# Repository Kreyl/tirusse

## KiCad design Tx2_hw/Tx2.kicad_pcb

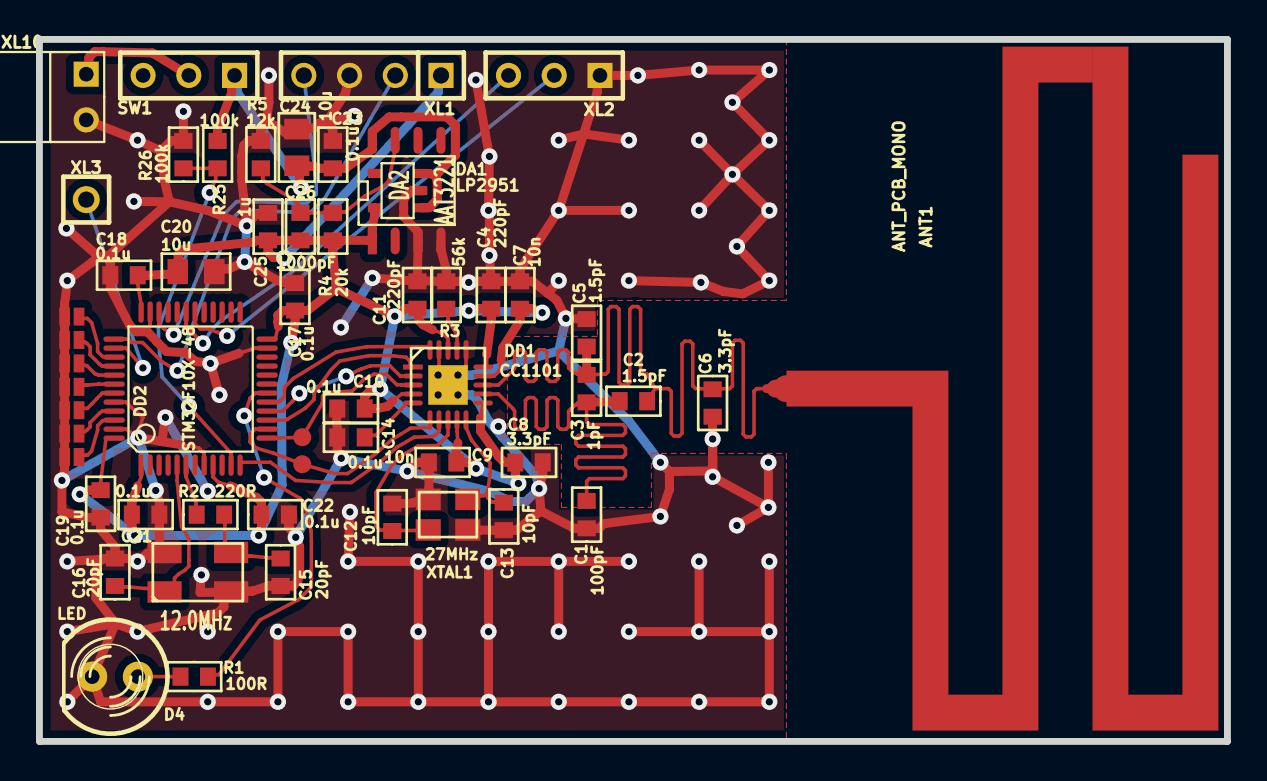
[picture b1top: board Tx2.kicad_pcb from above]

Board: 2 copper layers, 66.0 x 39.0 mm, 55 parts (0 on the bottom side), 35 nets.

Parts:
ANT1: ANT_PCB_MONO; ANT_868_MEANDER
C1: 100pF; CAP_0603
C2, C5: 1.5pF; CAP_0603
C3: 1pF; CAP_0603
C4, C11: 220pF; CAP_0603
C6, C8: 3.3pF; CAP_0603
C7, C9: 10n; CAP_0603
C10, C14, C17, C18, C19, C21, C22, C23: 0.1u; CAP_0603
C12, C13: 10pF; CAP_0603
C15, C16: 20pF; CAP_0603
C20, C24: 10u; CAP_0805
C25: 1u; CAP_0603
C26: 1000pF; CAP_0603
D4: LED; LED-5MM
DA1: LP2951; SO8E
DA2: AAT3221; SOT23-5
DD1: CC1101; QFN20
DD2: STM32F10X-48; LQFP48
F1, F2, F3, F4, F5, F6, F7: FUSE0R; SOLDERFUSE
R1: 100R; RES_0603
R2: 220R; RES_0603
R3: 56k; RES_0603
R4: 20k; RES_0603
R5: 12k; RES_0603
R25, R26: 100k; RES_0603
SW1: SWITCH; SIL-3
TP1, TP2: TESTPOINT; TESTPOINT_1MM
XL1: ST_SWD; SIL-4
XL2: CONN_3; SIL-3
XL3: CONN_1; SIL-1
XL10: PWRCONN; PWRCON2PIN
XTAL1: 27MHz; CRYSTAL_03225C4
XTAL2: 12.0MHz; CRYSTAL_0503x4-4

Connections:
+3.3V: C4.1, C7.1, C8.1, C9.1, C10.1, C11.1, C17.1, C18.1, C19.1, C20.1, C21.1, C22.1, C25.1, C26.1, DA1.1, DA2.5, DD1.4, DD1.9, DD1.11, DD1.14, DD1.15, DD1.18, DD2.1, DD2.9, DD2.24, DD2.36, DD2.48, R4.1, XL1.1
+BATT: C23.1, C24.1, DA1.8, DA2.1, DA2.3, R25.1, SW1.1
/BAT: SW1.2, XL10.1
/CC_CS: DD1.7, DD2.12
/CC_GDO0: DD1.6, DD2.14, TP1.1
/CC_GDO2: DD1.3, DD2.13, TP2.1
/CC_MISO: DD1.2, DD2.16
/CC_MOSI: DD1.20, DD2.17
/CC_SCK: DD1.1, DD2.15
/Debug: DD2.38, XL3.1
/RF1: C1.2, C2.2, C3.1, DD1.12
/RF2: ANT1.1, C2.1, C3.2, C5.1, C6.1, DD1.13
/RX1: DD2.31, XL2.3
/SWCLK: DD2.37, XL1.2
/SWDIO: DD2.34, XL1.4
/TX1: DD2.30, XL2.2
/UBat_2: DD2.11, R25.2, R26.1
GND: C1.1, C4.2, C5.2, C6.2, C7.2, C8.2, C9.2, C10.2, C11.2, C12.2, C13.2, C14.2, C15.2, C16.2, C17.2, C18.2, C19.2, C20.2, C21.2, C22.2, C23.2, C24.2, C25.2, D4.C, DA1.3, DA1.4, DA2.2, DD1.16, DD1.19, DD1.PAD, DD2.8, DD2.23, DD2.35, DD2.44, DD2.47, F1.2, F2.2, F3.2, F4.2, F5.2, F6.2, F7.2, R3.2, R5.2, R26.2, XL1.3, XL2.1, XL10.2, XTAL1.H, XTAL2.H
unnamed: C12.1, DD1.8, XTAL1.1
unnamed: C13.1, DD1.10, XTAL1.2
unnamed: DD2.18, R1.2
unnamed: DD1.17, R3.1
unnamed: C14.1, DD1.5
unnamed: DD2.42, F4.1
unnamed: DD2.43, F5.1
unnamed: DD2.39, F1.1
unnamed: DD2.40, F2.1
unnamed: DD2.41, F3.1
unnamed: DD2.6, R2.1
unnamed: C16.1, DD2.5, XTAL2.1
unnamed: C15.1, R2.2, XTAL2.2
unnamed: DD2.46, F7.1
unnamed: DD2.45, F6.1
unnamed: C26.2, DA1.7, R4.2, R5.1
unnamed: D4.A, R1.1

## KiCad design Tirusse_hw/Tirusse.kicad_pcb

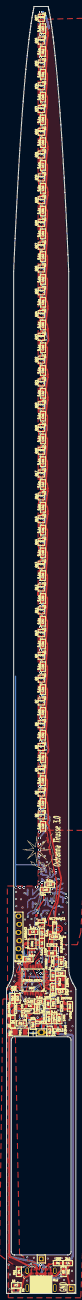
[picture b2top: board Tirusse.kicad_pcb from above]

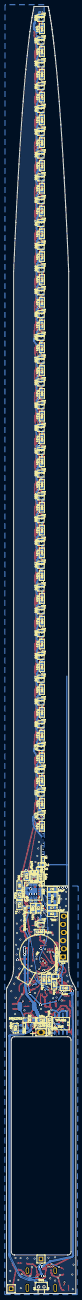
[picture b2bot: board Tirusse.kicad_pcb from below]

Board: 4 copper layers, 21.6 x 401.0 mm, 237 parts (111 on the bottom side), 134 nets.

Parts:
ANT1: ANT_PCB_MONO_2PIN; Tirusse868_inverted
BLN1: BALUN868JOHANSON; BALUN_JOHANSON868
C1: 100pF; CAP_0402
C2, C3: *; CAP_0402
C4: 2u2; CAP_0603_Silks
C5, C6, C9, C12, C13, C14, C15, C16, C17, C21, C22, C23, C24, C27, C28, C29, C30, C31, C32, C33, C34, C35, C36, C37, C38, C39, C40, C41, C42, C43, C44, C45, C46, C47, C48, C49, C50, C51, C52, C53, C54, C55, C56, C57, C58, C59, C60, C61, C62, C63, C64, C65, C66, C67, C68, C69, C70, C71, C72, C73, C74, C75, C76, C77, C78, C79, C80, C81, C82, C83, C84, C85, C86, C87, C88, C89, C90, C91, C92, C93, C94, C95, C96, C97, C98, C99, C100, C101, C107: 0.1u; CAP_0603_Silks
C7, C8, C10, C18: 18pF; CAP_0603_Silks
C11, C25, C102, C103: 1u; CAP_0603_Silks
C19: 10u; CAP_0603
C20, C104, C105, C106: 10u; CAP_0603_Silks
C26: 10n; CAP_0603_Silks
D1: LED; LED_0603_ch
D2, D3: PMEG2020; SOD323
DA1: MC74VHC1; SOT23-5
DA2: MCP1700; SOT23-3A
DA3: TP4056; SO8_150MIL
DD1: LSM6DS3; 14_3x2d5_p0d5
DD2: CC1101; QFN20
DD3: STM32L433Cx; LQFP48
L1: *; IND_0402
L2, L3: BLM15AG102SN1; IND_0402
Logo1: Logo; Ostranna_12d7_10d1
M1: MOTOR_NO_CONTACTS; Motor_no_Contacts
Q1, Q2, Q3, Q4, Q5, Q6, Q7, Q8, Q9, Q10, Q11, Q12, Q13, Q14, Q15, Q16, Q17, Q18, Q19, Q20, Q21, Q22, Q23, Q24, Q25, Q26, Q27, Q28, Q29, Q30, Q31, Q32, Q33, Q34, Q35, Q36, Q37, Q38, Q39, Q40, Q41, Q42, Q43, Q44, Q45, Q46, Q47, Q48, Q49, Q50, Q51, Q52, Q53, Q54, Q55, Q56, Q57, Q58, Q59, Q60, Q61, Q62, Q63, Q64, Q65, Q66, Q67, Q68, Q69, Q70, Q71, Q72, Q73, Q74: LED_RGB_WS2812B_2020; LED_2020_WS2812
R1: 2R0; RES_0603
R2, R6: 56k; RES_0603
R3, R7: 1k; RES_0603
R4, R5: 5k1; RES_0603
R8, R9, R11, R17, R18, R19, R21: 100k; RES_0603
R10: 0R2; RES_1206
R12, R15, R16: 10k; RES_0603
R13: 1M; RES_0603
R14: 1.2k; RES_0603
R20: 20k; RES_0603
SW1: BUTTON_H; BTN_IT1198
TP1, TP2: TESTPOINT; TESTPOINT_1MM
VT1: DMG2302; SOT23-3
VT2, VT4: IRLML6401; SOT23-3
VT3: IRLML9303; SOT23-3
VT5, VT6: 2N7002; SOT23-3
VT7: BC848; SOT23-3
XL1: CONN_6; PLS-6_LOCK
XL2: USB_C; USB_C_MOLEX_1054500101
XL3, XL4: CONN_1; Oval3x1.5
XL5, XL7: CONN_1; PLS-1Square
XL6: CONN_1; PLS-1Oval
XTAL1: 27MHz; 03225C4
XTAL2: 12MHz; 03225C4

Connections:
+3v3: C20.2, C21.1, C22.1, C23.1, C24.1, C103.1, DA2.2 (OUT), DD3.1 (VBAT), DD3.24 (VDD), DD3.36 (VDDUSB), DD3.48 (VDD), L2.2, L3.1, XL1.1
+BATT: R8.1, R13.1, R19.1, VT3.3 (D), VT4.3 (D)
+PwrUnst: C102.1, D3.C, DA2.3 (IN), VT4.2 (S)
/+5V_MID: C104.2, DA3.4 (Vcc), DA3.8 (CE), R10.2
/+5V_USB: D3.A, R1.1, R10.1, R16.1, VT4.1 (G), XL2.A4 (VBUS), XL2.A9 (VBUS), XL2.B4 (VBUS), XL2.B9 (VBUS)
/+BAT_IN: C19.2, C105.2, C106.2, D2.C, DA3.5 (BAT), R9.1, R12.1, VT2.2 (S), VT3.2 (S), XL3.1, XL6.1
/ACC_CS: DD1.12 (CS), DD3.25 (PB12/CK3/SAI1FSA)
/ACC_INT1: DD1.4 (INT1), DD3.2 (WKUP2/RTC_OUT/PC13)
/ACC_MISO: DD1.1 (SA0/SDO), DD3.27 (PB14/MISO2/SDA2/T15C1/T1C2N/SAI1MCLKA)
/ACC_MOSI: DD1.14 (SDA/SDI), DD3.28 (PB15/MOSI2/T15C2/T1C3N/SAI1SDA)
/ACC_PWR: C5.1, C6.1, DD1.5 (VDDIO), DD1.8 (VDD), DD3.22 (PB11/T2C4/SDA2/RX3/LPTX1)
/ACC_SCK: DD1.13 (SCL/SCK), DD3.26 (PB13/SCK2/SCL2/T1C1N/T15C1N/SAI1SCKA)
/ADC_BAT: DD3.19 (PB1/T1C3N/LPTIM2_IN1/ADC16), R8.2, R11.1
/ADC_BAT_EN: DD3.18 (PB0/T1C2N/CK3/SAI1EXTCLK/ADC15), R18.1, VT6.1 (G)
/ANT1: C1.1, C2.1, L1.2
/ANT2: ANT1.1, C3.1, L1.1
/CC_CS: DD2.7 (CSn), DD3.38 (T2C1ETR/RX2/PA15), R2.1
/CC_GDO0: DD2.6 (GDO0), DD3.14 (ADC9/SAI1FSB/LPTIM2_OUT/DAC1/CK2/PA4), TP1.1
/CC_MISO: DD2.2 (SO(GDO1)), DD3.16 (ADC11/T16C1/MISO1/PA6)
/CC_MOSI: DD2.20 (SI), DD3.17 (ADC12/T1C1N/SCL3/MOSI1/PA7)
/CC_SCK: DD2.1 (SCLK), DD3.15 (ADC10/T2C1ETR/DAC2/SCK1/PA5)
/DIN0: DA1.4 (OutY), Q1.3 (DIN)
/IS_CHARGING: DA3.7 (~CHRG), DD3.10 (ADC5/WKUP1/T2C1ETR/PA0)
/MCU_VDDA: C25.1, C26.1, DD3.9 (VDDA/VREF+), L3.2
/NPX1_CTRL: DA1.2 (InA), DD3.41 (PB5/MOSI1/MOSI3/CK1/LPTIM1_IN1/SAI1SDB)
/NPX_PWR: C27.1, C28.1, C29.1, C30.1, C31.1, C32.1, C33.1, C34.1, C35.1, C36.1, C37.1, C38.1, C39.1, C40.1, C41.1, C42.1, C43.1, C44.1, C45.1, C46.1, C47.1, C48.1, C49.1, C50.1, C51.1, C52.1, C53.1, C54.1, C55.1, C56.1, C57.1, C58.1, C59.1, C60.1, C61.1, C62.1, C63.1, C64.1, C65.1, C66.1, C67.1, C68.1, C69.1, C70.1, C71.1, C72.1, C73.1, C74.1, C75.1, C76.1, C77.1, C78.1, C79.1, C80.1, C81.1, C82.1, C83.1, C84.1, C85.1, C86.1, C87.1, C88.1, C89.1, C90.1, C91.1, C92.1, C93.1, C94.1, C95.1, C96.1, C97.1, C98.1, C99.1, C100.1, C101.2, DA1.5 (Vcc), Q1.4 (VDD), Q2.4 (VDD), Q3.4 (VDD), Q4.4 (VDD), Q5.4 (VDD), Q6.4 (VDD), Q7.4 (VDD), Q8.4 (VDD), Q9.4 (VDD), Q10.4 (VDD), Q11.4 (VDD), Q12.4 (VDD), Q13.4 (VDD), Q14.4 (VDD), Q15.4 (VDD), Q16.4 (VDD), Q17.4 (VDD), Q18.4 (VDD), Q19.4 (VDD), Q20.4 (VDD), Q21.4 (VDD), Q22.4 (VDD), Q23.4 (VDD), Q24.4 (VDD), Q25.4 (VDD), Q26.4 (VDD), Q27.4 (VDD), Q28.4 (VDD), Q29.4 (VDD), Q30.4 (VDD), Q31.4 (VDD), Q32.4 (VDD), Q33.4 (VDD), Q34.4 (VDD), Q35.4 (VDD), Q36.4 (VDD), Q37.4 (VDD), Q38.4 (VDD), Q39.4 (VDD), Q40.4 (VDD), Q41.4 (VDD), Q42.4 (VDD), Q43.4 (VDD), Q44.4 (VDD), Q45.4 (VDD), Q46.4 (VDD), Q47.4 (VDD), Q48.4 (VDD), Q49.4 (VDD), Q50.4 (VDD), Q51.4 (VDD), Q52.4 (VDD), Q53.4 (VDD), Q54.4 (VDD), Q55.4 (VDD), Q56.4 (VDD), Q57.4 (VDD), Q58.4 (VDD), Q59.4 (VDD), Q60.4 (VDD), Q61.4 (VDD), Q62.4 (VDD), Q63.4 (VDD), Q64.4 (VDD), Q65.4 (VDD), Q66.4 (VDD), Q67.4 (VDD), Q68.4 (VDD), Q69.4 (VDD), Q70.4 (VDD), Q71.4 (VDD), Q72.4 (VDD), Q73.4 (VDD), Q74.4 (VDD), VT2.3 (D)
/NPX_PWR_EN: DD3.42 (PB6/SCL1/T16C1N/TX1/SAI1FSB), R17.2, VT5.1 (G)
/PWRBTN1: R15.1, SW1.1, VT3.1 (G)
/PWRBTN2: C107.1, R13.2, SW1.2
/RF1: BLN1.4 (Bal2), DD2.12 (RF_P)
/RF2: BLN1.3 (Bal1), DD2.13 (RF_N)
/RF3: BLN1.1 (Unbal), C1.2
/SWCLK: DD3.37 (SWCLK/PA14), XL1.2
/SWDIO: DD3.34 (SWDIO/PA13), XL1.4
/UART_RX: DD3.31 (T1C3/SDA1/SAI1SDA/RX1/PA10), XL1.6
/UART_TX: DD3.30 (T1C2/SCL1/SAI1FSA/TX1/PA9), XL1.5
/USB_D+: DD3.33 (USB_DP/T1ETR/MOSI1/PA12), XL2.A6 (D+), XL2.B6 (D+)
/USB_D-: DD3.32 (USB_DM/T1C4/MISO1/PA11), XL2.A7 (D-), XL2.B7 (D-)
/USB_DETECT: DD3.12 (ADC7/WKUP4/T15C1/T2C3/LP1TX/TX2/PA2), R16.2, R20.1
/VIBRO_OUT: D2.A, VT1.3 (D), XL4.1
/Vibro_CTRL: DD3.13 (ADC8/SAI1MCLKA/T15C2/T2C4/LP1RX/RX2/PA3), R21.2, VT1.1 (G)
GND: ANT1.2, BLN1.2 (GND), BLN1.5 (GND), BLN1.6 (GND), C2.2, C3.2, C4.2, C5.2, C6.2, C7.2, C8.2, C9.1, C10.2, C11.2, C12.2, C13.2, C14.2, C15.2, C16.2, C17.2, C18.2, C19.1, C20.1, C21.2, C22.2, C23.2, C24.2, C25.2, C26.2, C27.2, C28.2, C29.2, C30.2, C31.2, C32.2, C33.2, C34.2, C35.2, C36.2, C37.2, C38.2, C39.2, C40.2, C41.2, C42.2, C43.2, C44.2, C45.2, C46.2, C47.2, C48.2, C49.2, C50.2, C51.2, C52.2, C53.2, C54.2, C55.2, C56.2, C57.2, C58.2, C59.2, C60.2, C61.2, C62.2, C63.2, C64.2, C65.2, C66.2, C67.2, C68.2, C69.2, C70.2, C71.2, C72.2, C73.2, C74.2, C75.2, C76.2, C77.2, C78.2, C79.2, C80.2, C81.2, C82.2, C83.2, C84.2, C85.2, C86.2, C87.2, C88.2, C89.2, C90.2, C91.2, C92.2, C93.2, C94.2, C95.2, C96.2, C97.2, C98.2, C99.2, C100.2, C101.1, C102.2, C103.2, C104.1, C105.1, C106.1, C107.2, D1.C, DA1.1 (~OE), DA1.3 (GND), DA2.1 (GND), DA3.1 (TEMP), DA3.3 (GND), DD1.2 (SDx), DD1.3 (SCx), DD1.6 (GND), DD1.7 (GND), DD2.16 (GND), DD2.19 (GND), DD2.PAD (GND), DD3.8 (VSSA/VREF-), DD3.23 (VSS), DD3.35 (VSS), DD3.44 (BOOT0/PH3), DD3.47 (VSS), Q1.2 (GND), Q2.2 (GND), Q3.2 (GND), Q4.2 (GND), Q5.2 (GND), Q6.2 (GND), Q7.2 (GND), Q8.2 (GND), Q9.2 (GND), Q10.2 (GND), Q11.2 (GND), Q12.2 (GND), Q13.2 (GND), Q14.2 (GND), Q15.2 (GND), Q16.2 (GND), Q17.2 (GND), Q18.2 (GND), Q19.2 (GND), Q20.2 (GND), Q21.2 (GND), Q22.2 (GND), Q23.2 (GND), Q24.2 (GND), Q25.2 (GND), Q26.2 (GND), Q27.2 (GND), Q28.2 (GND), Q29.2 (GND), Q30.2 (GND), Q31.2 (GND), Q32.2 (GND), Q33.2 (GND), Q34.2 (GND), Q35.2 (GND), Q36.2 (GND), Q37.2 (GND), Q38.2 (GND), Q39.2 (GND), Q40.2 (GND), Q41.2 (GND), Q42.2 (GND), Q43.2 (GND), Q44.2 (GND), Q45.2 (GND), Q46.2 (GND), Q47.2 (GND), Q48.2 (GND), Q49.2 (GND), Q50.2 (GND), Q51.2 (GND), Q52.2 (GND), Q53.2 (GND), Q54.2 (GND), Q55.2 (GND), Q56.2 (GND), Q57.2 (GND), Q58.2 (GND), Q59.2 (GND), Q60.2 (GND), Q61.2 (GND), Q62.2 (GND), Q63.2 (GND), Q64.2 (GND), Q65.2 (GND), Q66.2 (GND), Q67.2 (GND), Q68.2 (GND), Q69.2 (GND), Q70.2 (GND), Q71.2 (GND), Q72.2 (GND), Q73.2 (GND), Q74.2 (GND), R4.1, R5.1, R6.2, R14.2, R17.1, R18.2, R20.2, R21.1, VT1.2 (S), VT5.2 (S), VT6.2 (S), VT7.2 (E), XL1.3, XL2.A1 (GND), XL2.A12 (GND), XL2.B1 (GND), XL2.B12 (GND), XL5.1, XL7.1, XTAL1.H, XTAL2.H
unnamed: C4.1, R1.2
unnamed: C18.1, R7.2, XTAL2.2
unnamed: D1.A, R3.1
unnamed: DA3.2 (PROG), R14.1
unnamed: C9.2, DD2.5 (DCOUPL)
unnamed: DD2.17 (RBIAS), R6.1
unnamed: C7.1, DD2.8 (XOSC_Q1), XTAL1.1
unnamed: C8.1, DD2.10 (XOSC_Q2), XTAL1.2
unnamed: DD3.4 (OC32OUT/PC15), TP2.1
unnamed: DD3.45 (PB8/SDIO_D4/T16C1/SCL1/SAI1MCLKA), R3.2
unnamed: C10.1, DD3.5 (PH0/OSCIN), XTAL2.1
unnamed: DD3.6 (PH1/OSCOUT), R7.1
unnamed: Q1.1 (DOUT), Q2.3 (DIN)
unnamed: Q2.1 (DOUT), Q3.3 (DIN)
unnamed: Q3.1 (DOUT), Q4.3 (DIN)
unnamed: Q4.1 (DOUT), Q5.3 (DIN)
unnamed: Q5.1 (DOUT), Q6.3 (DIN)
unnamed: Q6.1 (DOUT), Q7.3 (DIN)
unnamed: Q7.1 (DOUT), Q8.3 (DIN)
unnamed: Q8.1 (DOUT), Q9.3 (DIN)
unnamed: Q9.1 (DOUT), Q10.3 (DIN)
unnamed: Q10.1 (DOUT), Q11.3 (DIN)
unnamed: Q11.1 (DOUT), Q12.3 (DIN)
unnamed: Q12.1 (DOUT), Q13.3 (DIN)
unnamed: Q13.1 (DOUT), Q14.3 (DIN)
unnamed: Q14.1 (DOUT), Q15.3 (DIN)
unnamed: Q15.1 (DOUT), Q16.3 (DIN)
unnamed: Q16.1 (DOUT), Q17.3 (DIN)
unnamed: Q17.1 (DOUT), Q18.3 (DIN)
unnamed: Q18.1 (DOUT), Q19.3 (DIN)
unnamed: Q19.1 (DOUT), Q20.3 (DIN)
unnamed: Q20.1 (DOUT), Q21.3 (DIN)
unnamed: Q21.1 (DOUT), Q22.3 (DIN)
unnamed: Q22.1 (DOUT), Q23.3 (DIN)
unnamed: Q23.1 (DOUT), Q24.3 (DIN)
unnamed: Q24.1 (DOUT), Q25.3 (DIN)
unnamed: Q25.1 (DOUT), Q26.3 (DIN)
unnamed: Q26.1 (DOUT), Q27.3 (DIN)
unnamed: Q27.1 (DOUT), Q28.3 (DIN)
unnamed: Q28.1 (DOUT), Q29.3 (DIN)
unnamed: Q29.1 (DOUT), Q30.3 (DIN)
unnamed: Q30.1 (DOUT), Q31.3 (DIN)
unnamed: Q31.1 (DOUT), Q32.3 (DIN)
unnamed: Q32.1 (DOUT), Q33.3 (DIN)
unnamed: Q33.1 (DOUT), Q34.3 (DIN)
unnamed: Q34.1 (DOUT), Q35.3 (DIN)
unnamed: Q35.1 (DOUT), Q36.3 (DIN)
unnamed: Q36.1 (DOUT), Q37.3 (DIN)
unnamed: Q37.1 (DOUT), Q38.3 (DIN)
unnamed: Q38.1 (DOUT), Q39.3 (DIN)
unnamed: Q39.1 (DOUT), Q40.3 (DIN)
unnamed: Q40.1 (DOUT), Q41.3 (DIN)
unnamed: Q41.1 (DOUT), Q42.3 (DIN)
unnamed: Q42.1 (DOUT), Q43.3 (DIN)
unnamed: Q43.1 (DOUT), Q44.3 (DIN)
unnamed: Q44.1 (DOUT), Q45.3 (DIN)
unnamed: Q45.1 (DOUT), Q46.3 (DIN)
unnamed: Q46.1 (DOUT), Q47.3 (DIN)
unnamed: Q47.1 (DOUT), Q48.3 (DIN)
unnamed: Q48.1 (DOUT), Q49.3 (DIN)
unnamed: Q49.1 (DOUT), Q50.3 (DIN)
unnamed: Q50.1 (DOUT), Q51.3 (DIN)
unnamed: Q51.1 (DOUT), Q52.3 (DIN)
unnamed: Q52.1 (DOUT), Q53.3 (DIN)
unnamed: Q53.1 (DOUT), Q54.3 (DIN)
unnamed: Q54.1 (DOUT), Q55.3 (DIN)
unnamed: Q55.1 (DOUT), Q56.3 (DIN)
unnamed: Q56.1 (DOUT), Q57.3 (DIN)
unnamed: Q57.1 (DOUT), Q58.3 (DIN)
unnamed: Q58.1 (DOUT), Q59.3 (DIN)
unnamed: Q59.1 (DOUT), Q60.3 (DIN)
unnamed: Q60.1 (DOUT), Q61.3 (DIN)
unnamed: Q61.1 (DOUT), Q62.3 (DIN)
unnamed: Q62.1 (DOUT), Q63.3 (DIN)
unnamed: Q63.1 (DOUT), Q64.3 (DIN)
unnamed: Q64.1 (DOUT), Q65.3 (DIN)
unnamed: Q65.1 (DOUT), Q66.3 (DIN)
unnamed: Q66.1 (DOUT), Q67.3 (DIN)
unnamed: Q67.1 (DOUT), Q68.3 (DIN)
unnamed: Q68.1 (DOUT), Q69.3 (DIN)
unnamed: Q69.1 (DOUT), Q70.3 (DIN)
unnamed: Q70.1 (DOUT), Q71.3 (DIN)
unnamed: Q71.1 (DOUT), Q72.3 (DIN)
unnamed: Q72.1 (DOUT), Q73.3 (DIN)
unnamed: Q73.1 (DOUT), Q74.3 (DIN)
unnamed: R9.2, VT2.1 (G), VT5.3 (D)
unnamed: R11.2, VT6.3 (D)
unnamed: R19.2, VT7.1 (B)
unnamed: R12.2, R15.2, VT7.3 (C)
unnamed: R4.2, XL2.A5 (CC1)
unnamed: R5.2, XL2.B5 (CC2)
VCC: C11.1, C12.1, C13.1, C14.1, C15.1, C16.1, C17.1, DD2.4 (DVDD), DD2.9 (AVDD), DD2.11 (AVDD), DD2.14 (AVDD), DD2.15 (AVDD), DD2.18 (DGUARD), L2.1, R2.2

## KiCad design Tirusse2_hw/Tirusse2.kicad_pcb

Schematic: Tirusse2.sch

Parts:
C1: 100pF
C2, C4: 1.5pF
C3: 1pF
C5, C8: 3.3pF
C6, C11: 220pF
C7, C9: 10n
C10, C14: 0.1u
C12: 1u; CAP_0603
C13: 100u
C15, C18: 20pF; CAP_0402
C16, C17: 10pF; CAP_0402
C26, C27: 10u
C28, C29: 1u
C38, C39, C40, C43, C44: 0.1u; CAP_0402
C41: 10u; CAP_0805
D1: BAT54WS
D2: LED
D3: BAXXXC
DA1: NCP583SQ
DA4: MCP73832
DD1: CC1101
DD2: STM32F10X-48
F1, F2, F3, F4, F5, F6, F7: FUSE0R
L1, L6: 18nH; IND_0402
L2, L3, L4, L5: 12nH; IND_0402
L7, L8: 22uH; IND_1812
Q1: IRLML6302
R1: 56k
R2: *; RES_0603
R3: 220R; RES_0402
R7, R9: 330k
R10: 2k
R19: 1k; RES_0402
SW1: SWITCH
TP2, TP3: TESTPOINT
XL1, XL4, XL8: CONN_1
XL2, XL3, XL7: CONN_1
XL5: CONN_3
XL6: ST_SWD
XL10: USB_MICRO_B
XTAL1: 27MHz; 03225
XTAL2: 12.0MHz; 0532

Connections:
+3.3V: C6.1, C7.1, C8.1, C9.1, C10.1, C11.1, C29.1, C38.1, C39.1, C40.1, C41.1, C43.1, C44.1, DA1.3 (Vout), DD1.4 (DVDD), DD1.9 (AVDD), DD1.11 (AVDD), DD1.14 (AVDD), DD1.15 (AVDD), DD1.18 (DGUARD), DD2.1 (VBAT), DD2.9 (VDDA), DD2.24 (VDD1), DD2.36 (VDD2), DD2.48 (VDD3), XL6.1 (Vdd)
+5V: C27.1, D3.1, DA4.4 (VDD), R19.2, XL10.1 (UVcc)
+BATT: C12.1, C26.1, D3.2, DA4.3 (VBAT), F2.2, Q1.2 (S), R7.1, SW1.1
/BAT: SW1.2, XL2.1
/CC_CS: DD1.7 (CSn), DD2.12 (ADC1-2/T2C3/T15C1/TX2/PA2)
/CC_GDO0: DD1.6 (GDO0), DD2.14 (ADC1-4/DAC1/CK2/PA4), TP2.1
/CC_GDO2: DD1.3 (GDO2), DD2.13 (ADC1-3/T2C4/T15C2/RX2/PA3), TP3.1
/CC_MISO: DD1.2 (SO(GDO1)), DD2.16 (ADC1-6/T3C1/MISO1/PA6)
/CC_MOSI: DD1.20 (SI), DD2.17 (ADC1-7/T3C2/MOSI1/PA7)
/CC_SCK: DD1.1 (SCLK), DD2.15 (ADC1-5/DAC2/SCK1/PA5)
/Charge: DA4.1 (STAT), DD2.33 (USBDP/PA12)
/Debug: DD2.38 (JTDI/PA15), XL7.1
/PWR_IN: C28.1, D3.3, DA1.1 (EN), DA1.4 (Vin), F2.1
/RF1: DD1.12 (RF_P), L2.2
/RF2: DD1.13 (RF_N), L5.2
/RX1: DD2.31 (T1C3/RX1/PA10), XL5.3
/SWCLK: DD2.37 (SWCLK/JTCK/PA14), XL6.2 (SWCLK)
/SWDIO: DD2.34 (SWDIO/JTMS/PA13), XL6.4 (SWDIO)
/TX1: DD2.30 (T1C2/TX1/PA9), XL5.2 (PM)
/UBat_2: DD2.11 (ADC1-1/T2C2/PA1), R7.2, R9.1
GND: C1.1, C4.2, C5.2, C6.2, C7.2, C8.2, C9.2, C10.2, C11.2, C12.2, C13.2, C14.2, C15.2, C16.2, C17.2, C18.2, C26.2, C27.2, C28.2, C29.2, C38.2, C39.2, C40.2, C41.2, C43.2, C44.2, D1.A, D2.C, DA1.2 (GND), DA4.2 (GND), DD1.16 (GND), DD1.19 (GND), DD1.PAD (GND), DD2.8 (VSSA), DD2.23 (VSS1), DD2.35 (VSS2), DD2.44 (BOOT0), DD2.47 (VSS3), F3.2, F4.2, F5.2, F6.2, F7.2, R1.2, R9.2, R10.2, XL1.1, XL3.1, XL5.1, XL6.3 (GND), XL8.1, XL10.4 (UGND), XL10.5 (UID), XL10.SHLD, XTAL1.H, XTAL2.H
unnamed: C17.1, DD1.10 (XOSC_Q2), XTAL1.2
unnamed: C14.1, DD1.5 (DCOUPL)
unnamed: DD1.17 (RBIAS), R1.1
unnamed: C1.2, L1.1
unnamed: DD2.10 (ADC1-0/WKUP/PA0), R19.1
unnamed: C2.2, C3.1, L1.2, L2.1
unnamed: DA4.5 (PROG), R10.1
unnamed: C5.1, L3.1, L4.2
unnamed: L4.1, XL4.1
unnamed: C2.1, L3.2, L6.1
unnamed: C16.1, DD1.8 (XOSC_Q1), XTAL1.1
unnamed: C3.2, C4.1, L5.1, L6.2
unnamed: DD2.43 (PB7/SDA1/T4C2/T17C1N), F7.1
unnamed: DD2.41 (PB5/(T3C2)), F5.1
unnamed: DD2.40 (PB4/JTRST/(T3C1)), F4.1
unnamed: DD2.39 (PB3/JTDO/(T2C2)), F3.1
unnamed: DD2.42 (PB6/SCL1/T4C1/T16C1N), F6.1
unnamed: DD2.6 (OSCOUT/(PD1)), R3.1
unnamed: C18.1, DD2.5 (OSCIN/(PD0)), XTAL2.1
unnamed: C15.1, R3.2, XTAL2.2
unnamed: DD2.18 (PB0/T3C3/ADC1-8), F1.1, Q1.1 (G)
unnamed: C13.1, D2.A, L7.1, L8.1, R2.2
unnamed: D1.C, F1.2, L7.2, L8.2, Q1.3 (D), R2.1

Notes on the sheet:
USB connect detector
DEBUG TX/RX
USB
Radio
CPU
Programming
3.0V 150mA power regulator
Li-Ion charger 2k => 0.5 A
Battery meter
Power
Debug connector
Battery
Address settings

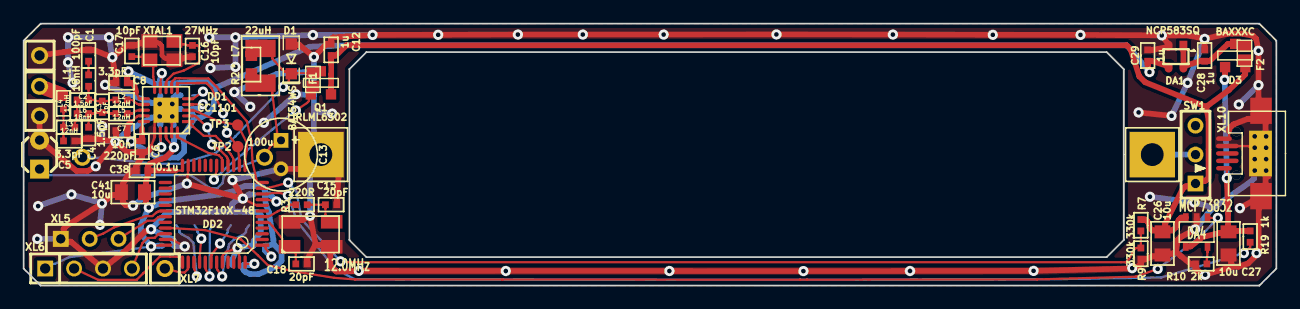
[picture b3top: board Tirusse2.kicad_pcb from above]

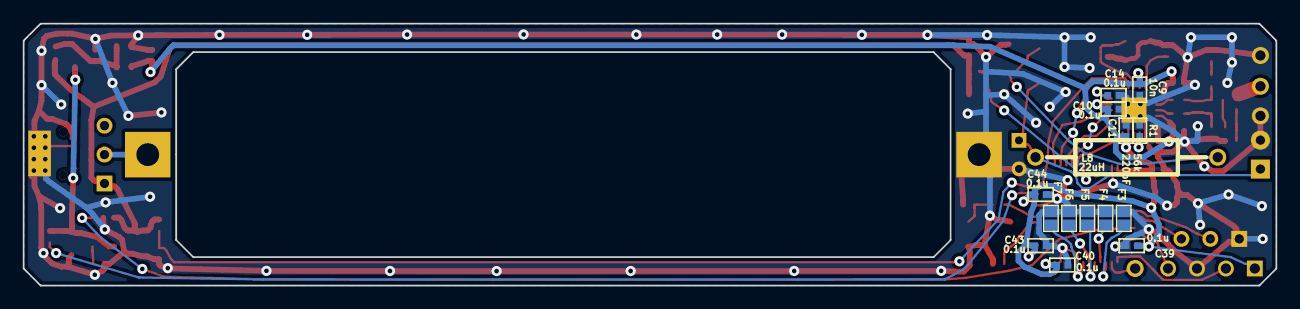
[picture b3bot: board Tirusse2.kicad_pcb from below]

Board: 2 copper layers, 110.0 x 23.0 mm, 72 parts (15 on the bottom side), 44 nets.

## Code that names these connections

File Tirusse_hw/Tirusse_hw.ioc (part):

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Mcu.Name=STM32L433C(B-C)Tx
Mcu.Package=LQFP48
Mcu.UserName=STM32L433CCTx
PA0.Mode=SYS_WakeUp0
PA0.Signal=SYS_WKUP1
PA10.Mode=Asynchronous
PA10.Signal=USART1_RX
PA11.Mode=Device
PA11.Signal=USB_DM
PA12.Mode=Device
PA12.Signal=USB_DP
PA13\ (JTMS-SWDIO).Mode=Serial_Wire
PA13\ (JTMS-SWDIO).Signal=SYS_JTMS-SWDIO
PA14\ (JTCK-SWCLK).Mode=Serial_Wire
PA14\ (JTCK-SWCLK).Signal=SYS_JTCK-SWCLK
PA2.Mode=SYS_WakeUp3
PA2.Signal=SYS_WKUP4
PA5.Mode=Full_Duplex_Master
PA5.Signal=SPI1_SCK
PA6.Mode=Full_Duplex_Master
PA6.Signal=SPI1_MISO
PA7.Mode=Full_Duplex_Master
PA7.Signal=SPI1_MOSI
PA9.Mode=Asynchronous
PA9.Signal=USART1_TX
PB13.Mode=Full_Duplex_Master
PB13.Signal=SPI2_SCK
PB14.Mode=Full_Duplex_Master
PB14.Signal=SPI2_MISO
PB15.Mode=Full_Duplex_Master
PB15.Signal=SPI2_MOSI
PB3\ (JTDO-TRACESWO).Mode=TX_Only_Simplex_Unidirect_Master
PB3\ (JTDO-TRACESWO).Signal=SPI3_SCK
PB4\ (NJTRST).Signal=GPIO_Analog
PB5.Mode=TX_Only_Simplex_Unidirect_Master
PB5.Signal=SPI3_MOSI
PC13.Mode=SYS_WakeUp1
PC13.Signal=SYS_WKUP2
PH0-OSC_IN\ (PH0).Mode=HSE-External-Oscillator
PH0-OSC_IN\ (PH0).Signal=RCC_OSC_IN
PH1-OSC_OUT\ (PH1).Mode=HSE-External-Oscillator
PH1-OSC_OUT\ (PH1).Signal=RCC_OSC_OUT
RCC.HSE_VALUE=12000000
RCC.SYSCLKFreq_VALUE=20000000
RCC.SYSCLKSource=RCC_SYSCLKSOURCE_PLLCLK
board=custom

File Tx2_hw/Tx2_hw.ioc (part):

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Mcu.Name=STM32F100C(4-6)Tx
Mcu.Package=LQFP48
Mcu.UserName=STM32F100C4Tx
PA1.Signal=ADCx_IN1
PA10.Mode=Asynchronous
PA10.Signal=USART1_RX
PA13.Mode=Serial_Wire
PA13.Signal=SYS_JTMS-SWDIO
PA14.Mode=Serial_Wire
PA14.Signal=SYS_JTCK-SWCLK
PA15.Signal=GPIO_Output
PA2.Signal=GPIO_Output
PA3.Signal=S_TIM15_CH2
PA4.Signal=GPIO_Input
PA5.Mode=Full_Duplex_Master
PA5.Signal=SPI1_SCK
PA6.Mode=Full_Duplex_Master
PA6.Signal=SPI1_MISO
PA7.Mode=Full_Duplex_Master
PA7.Signal=SPI1_MOSI
PA9.Mode=Asynchronous
PA9.Signal=USART1_TX
PB0.Signal=S_TIM3_CH3
PB3.Signal=GPIO_Input
PB4.Signal=GPIO_Input
PB5.Signal=GPIO_Input
PB6.Signal=GPIO_Input
PB7.Signal=GPIO_Input
PB8.Signal=GPIO_Input
PB9.Signal=GPIO_Input
RCC.SYSCLKFreq_VALUE=8000000
board=custom

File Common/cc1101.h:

/*
 * cc1101.h
 *
 *  Created on: Feb 12, 2013
 *      Author: g.kruglov
 */

#ifndef CC1101_H_
#define CC1101_H_

/*
 * Low-level operations are here.
 * Pkt level at top side, and SPI at bottom.
 */

#include <inttypes.h>
#include "kl_lib_f100.h"
#include "cc1101defins.h"
#include "cc1101_rf_settings.h"
#include "lvl1_lckt.h"

// Pins
#define CC_GPIO     GPIOA
#define CC_GDO2     3
#define CC_GDO0     4
#define CC_SCK      5
#define CC_MISO     6
#define CC_MOSI     7
#define CC_CS       2

// SPI
#define CC_SPI      SPI1

enum CCState_t {ccIdle, ccSleeping, ccReceiving, ccTransmitting};

class cc1101_t {
private:
    uint8_t IState; // Inner CC state, returned as first byte
    EventSource IEvtSrcTx, IEvtSrcRx;
    // Pins
    void CsHi() { PinSet(CC_GPIO, CC_CS); }
    void CsLo() { PinClear(CC_GPIO, CC_CS); }
    bool GDO0IsHi() { return PinIsSet(CC_GPIO, CC_GDO0); }
    bool GDO2IsHi() { return PinIsSet(CC_GPIO, CC_GDO2); }
    void BusyWait() { while(PinIsSet(CC_GPIO, CC_MISO)); }
    // General
    uint8_t ReadWriteByte(uint8_t AByte);
    void RfConfig();
    int8_t RSSI_dBm(uint8_t ARawRSSI);
    // Registers and buffers
    void WriteRegister (const uint8_t Addr, const uint8_t AData);
    uint8_t ReadRegister (const uint8_t Addr);
    void WriteStrobe(uint8_t AStrobe);
    void WriteTX(uint8_t* Ptr, uint8_t Length);
    // Strobes
    void CReset()      { WriteStrobe(CC_SRES); }
    void EnterTX()     { WriteStrobe(CC_STX);  }
    void FlushTxFIFO() { WriteStrobe(CC_SFTX); }
    void GetState()    { WriteStrobe(CC_SNOP); }
    void EnterRX()     { WriteStrobe(CC_SRX);  }
    void FlushRxFIFO() { WriteStrobe(CC_SFRX); }
    void Recalibrate() {
        while (IState != CC_STB_IDLE) EnterIdle();
        WriteStrobe(CC_SCAL);
    }
public:
    CCState_t State;
    void Init();
    void SetChannel(uint8_t AChannel);
    void SetTxPower(uint8_t APwr) { WriteRegister(CC_PATABLE, APwr); }
    // Events
    void RegisterEvtRx(EventListener *PEvtLstnr, uint8_t EvtMask) { chEvtRegisterMask(&IEvtSrcRx, PEvtLstnr, EvtMask); }
    void RegisterEvtTx(EventListener *PEvtLstnr, uint8_t EvtMask) { chEvtRegisterMask(&IEvtSrcTx, PEvtLstnr, EvtMask); }
    // State change
    void TransmitSync(rPkt_t *pPkt);
    uint8_t ReceiveSync(uint32_t Timeout_ms, rPkt_t *pPkt);
    void TransmitAsync(rPkt_t *pPkt);
    void ReceiveAsync();
    void EnterIdle()  { WriteStrobe(CC_SIDLE); State = ccIdle; }
    void Sleep() { WriteStrobe(CC_SPWD); State = ccSleeping; }
    uint8_t ReadFIFO(rPkt_t *pPkt);
    // Inner use
    inline void IHandleAsync();
};

extern cc1101_t CC;

#endif /* CC1101_H_ */

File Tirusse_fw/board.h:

#pragma once

// ==== General ====
#define APP_NAME            "Tirusse"

#ifndef TRUE
#define TRUE 1
#endif

// Version of PCB
#define PCB_VER                 1

// MCU type as defined in the ST header.
#define STM32L433xx

// Freq of external crystal if any. Leave it here even if not used.
#define CRYSTAL_FREQ_HZ         12000000

// OS timer settings
#define STM32_ST_IRQ_PRIORITY   2
#define STM32_ST_USE_TIMER      2
#define SYS_TIM_CLK             (Clk.APB1FreqHz)    // Timer 5 is clocked by APB1

//  Periphery
#define I2C1_ENABLED            FALSE
#define I2C2_ENABLED            FALSE
#define I2C3_ENABLED            FALSE
#define SIMPLESENSORS_ENABLED   TRUE
#define BUTTONS_ENABLED         TRUE

#define ADC_REQUIRED            TRUE
#define STM32_DMA_REQUIRED      TRUE    // Leave this macro name for OS

#if 1 // ========================== GPIO =======================================
// EXTI
#define INDIVIDUAL_EXTI_IRQ_REQUIRED    FALSE

// Button
#define BTN_PIN         GPIOC, 13

// Battery
#define IS_CHARGING     GPIOA, 0
#define BAT_MEAS_EN     GPIOB, 0
#define BAT_ADC_PIN     GPIOB, 1, 16 // PB1, ADC channel 16

// Vibro
#define VIBRO_PIN       { GPIOA, 3, TIM15, 2, invNotInverted, omPushPull, 255 }

// Light
#define LED_PIN         { GPIOB, 8, TIM16, 1, invNotInverted, omPushPull, 255 }
// Npx LEDs
#define NPX_LED_CNT     74
#define NPX_SPI         SPI3
#define NPX_DATA_PIN    GPIOB, 5, AF6
#define NPX_PWR_PIN     GPIOB, 6

// USB
#define USB_DM          GPIOA, 11
#define USB_DP          GPIOA, 12
#define USB_AF          AF10
#define USB_DETECT_PIN  GPIOA, 2

// Radio: SPI, PGpio, Sck, Miso, Mosi, Cs, Gdo0
#define CC_Setup0       SPI1, GPIOA, 5,6,7, GPIOA,15, GPIOA,4

// UART
#define UART_GPIO       GPIOA
#define UART_TX_PIN     9
#define UART_RX_PIN     10

// Acc
#define ACG_IRQ_PIN     GPIOC, 13
#define ACG_CS_PIN      GPIOB, 12
#define ACG_SCK_PIN     GPIOB, 13, omPushPull, pudNone, AF5
#define ACG_MISO_PIN    GPIOB, 14, omPushPull, pudNone, AF5
#define ACG_MOSI_PIN    GPIOB, 15, omPushPull, pudNone, AF5
#define ACG_PWR_PIN     GPIOB, 11
#define ACG_SPI         SPI2

#endif // GPIO

#if 0 // =========================== I2C =======================================
// I2C
#define I2C1_GPIO       GPIOB
#define I2C1_SCL        8
#define I2C1_SDA        9
// I2C Alternate Function
#define I2C_AF          AF4
// i2cclkPCLK1, i2cclkSYSCLK, i2cclkHSI
#define I2C_CLK_SRC     i2cclkHSI
#define I2C_BAUDRATE_HZ 400000
// ==== I2C ====
#define I2C1_DMA_TX     STM32_DMA_STREAM_ID(1, 6)
#define I2C1_DMA_RX     STM32_DMA_STREAM_ID(1, 7)
#define I2C1_DMA_CHNL   3
#endif

#if ADC_REQUIRED // ======================= Inner ADC ==========================
// Clock divider: clock is generated from the APB2
#define ADC_CLK_DIVIDER		adcDiv2

// ADC channels
#define ADC_BATTERY_CHNL 	14
// ADC_VREFINT_CHNL
#define ADC_CHANNELS        { ADC_BATTERY_CHNL, ADC_VREFINT_CHNL }
#define ADC_CHANNEL_CNT     2   // Do not use countof(AdcChannels) as preprocessor does not know what is countof => cannot check
#define ADC_SAMPLE_TIME     ast24d5Cycles
#define ADC_OVERSAMPLING_RATIO  64   // 1 (no oversampling), 2, 4, 8, 16, 32, 64, 128, 256
#endif

#if 1 // =========================== DMA =======================================
// ==== Uart ====
// Remap is made automatically if required
#define UART_DMA_TX     STM32_DMA_STREAM_ID(2, 6)
#define UART_DMA_RX     STM32_DMA_STREAM_ID(2, 7)
#define UART_DMA_CHNL   2
#define UART_DMA_TX_MODE(Chnl) (STM32_DMA_CR_CHSEL(Chnl) | DMA_PRIORITY_LOW | STM32_DMA_CR_MSIZE_BYTE | STM32_DMA_CR_PSIZE_BYTE | STM32_DMA_CR_MINC | STM32_DMA_CR_DIR_M2P | STM32_DMA_CR_TCIE)
#define UART_DMA_RX_MODE(Chnl) (STM32_DMA_CR_CHSEL(Chnl) | DMA_PRIORITY_MEDIUM | STM32_DMA_CR_MSIZE_BYTE | STM32_DMA_CR_PSIZE_BYTE | STM32_DMA_CR_MINC | STM32_DMA_CR_DIR_P2M | STM32_DMA_CR_CIRC)

// ==== Npx ====
#define NPX_DMA         STM32_DMA_STREAM_ID(2, 2)  // SPI3 TX
#define NPX_DMA_REQ     3

// ==== ACG ====
#define ACG_DMA_TX      STM32_DMA_STREAM_ID(1, 5)
#define ACG_DMA_RX      STM32_DMA_STREAM_ID(1, 4)
#define ACG_DMA_CHNL    1

#if ADC_REQUIRED
#define ADC_DMA         STM32_DMA_STREAM_ID(1, 1)
#define ADC_DMA_MODE    STM32_DMA_CR_CHSEL(0) |   /* DMA1 Stream1 Channel0 */ \
                        DMA_PRIORITY_LOW | \
                        STM32_DMA_CR_MSIZE_HWORD | \
                        STM32_DMA_CR_PSIZE_HWORD | \
                        STM32_DMA_CR_MINC |       /* Memory pointer increase */ \
                        STM32_DMA_CR_DIR_P2M |    /* Direction is peripheral to memory */ \
                        STM32_DMA_CR_TCIE         /* Enable Transmission Complete IRQ */
#endif // ADC

#endif // DMA

#if 1 // ========================== USART ======================================
#define PRINTF_FLOAT_EN TRUE
#define UART_TXBUF_SZ   2048
#define UART_RXBUF_SZ   128
#define CMD_BUF_SZ      64

#define CMD_UART        USART1

#define CMD_UART_PARAMS \
    CMD_UART, UART_GPIO, UART_TX_PIN, UART_GPIO, UART_RX_PIN, \
    UART_DMA_TX, UART_DMA_RX, UART_DMA_TX_MODE(UART_DMA_CHNL), UART_DMA_RX_MODE(UART_DMA_CHNL), \
    uartclkHSI // Use independent clock

#endif

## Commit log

2022-05-30 Version 1 (Atmega-based)
2022-05-30 V2 with transmitter
2022-05-30 Old files removed
2022-06-25 Working on v3
2022-06-30 PCB sent to factory
2022-07-02 + Tx2 transmitter hw
2022-07-02 not needed
2022-07-12 FW first UART works, SetCurrClrs works
2022-07-14 Antenna matched
2022-07-18 + Radio works + Blade powered off and on * SCH modified to fix powerbtn control
2022-07-18 + Adc works
2022-07-18 To Sleep and back again by button
2022-07-18 + Gem
2022-07-18 + Battery indication
2022-07-18 + Tx2 fw started
2022-07-18 + sequences * SysTimer is now TIM2
2022-07-18 Switch to newer kl_lib
2022-07-18 + TIM15 used as timing src + Radio seems working
2022-07-19 + Battery measurement RC
2022-07-20 + Indication of PwrOn/PwrOff RC
2022-07-20 Indication made more clear
2022-07-24 Tirusse release
2022-07-24 Tx2 Dark Release
